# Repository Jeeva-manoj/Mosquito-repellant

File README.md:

# Mosquito-repellant
This EAGLE schematic can be used as a mosquito repellant, using ultrasonic waves

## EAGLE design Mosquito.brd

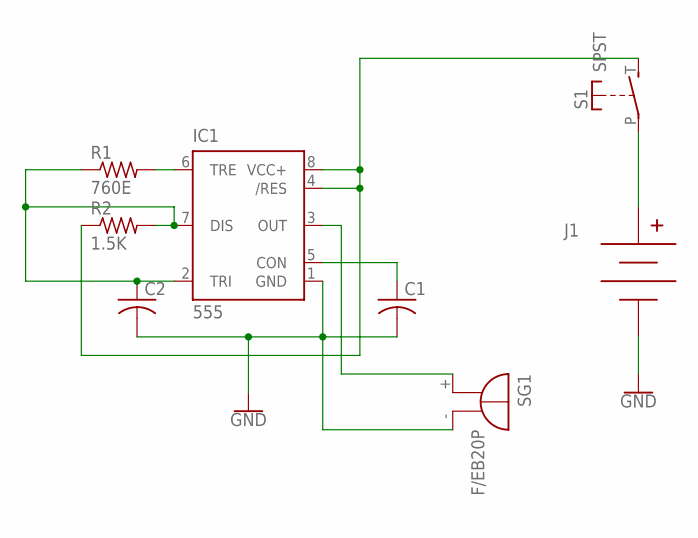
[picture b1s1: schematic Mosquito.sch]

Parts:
C1, C2: C-US025-024X044; C025-024X044
IC1: 555; DIP08
J1: BC9VPC
R1: 760E; 0204V
R2: 1.5K; 0204V
S1: SPST; JUDCOSPST
SG1: F/EB20P

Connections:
GND: C1.2, C2.2, IC1.1 (GND), J1.V-, SG1.-
unnamed: C2.1, IC1.2 (TRI), IC1.7 (DIS), R1.1, R2.2
unnamed: IC1.6 (TRE), R1.2
unnamed: IC1.3 (OUT), SG1.+
unnamed: C1.1, IC1.5 (CON)
unnamed: J1.V+, S1.P
unnamed: IC1.4 (/RES), IC1.8 (VCC+), R2.1, S1.T (S)

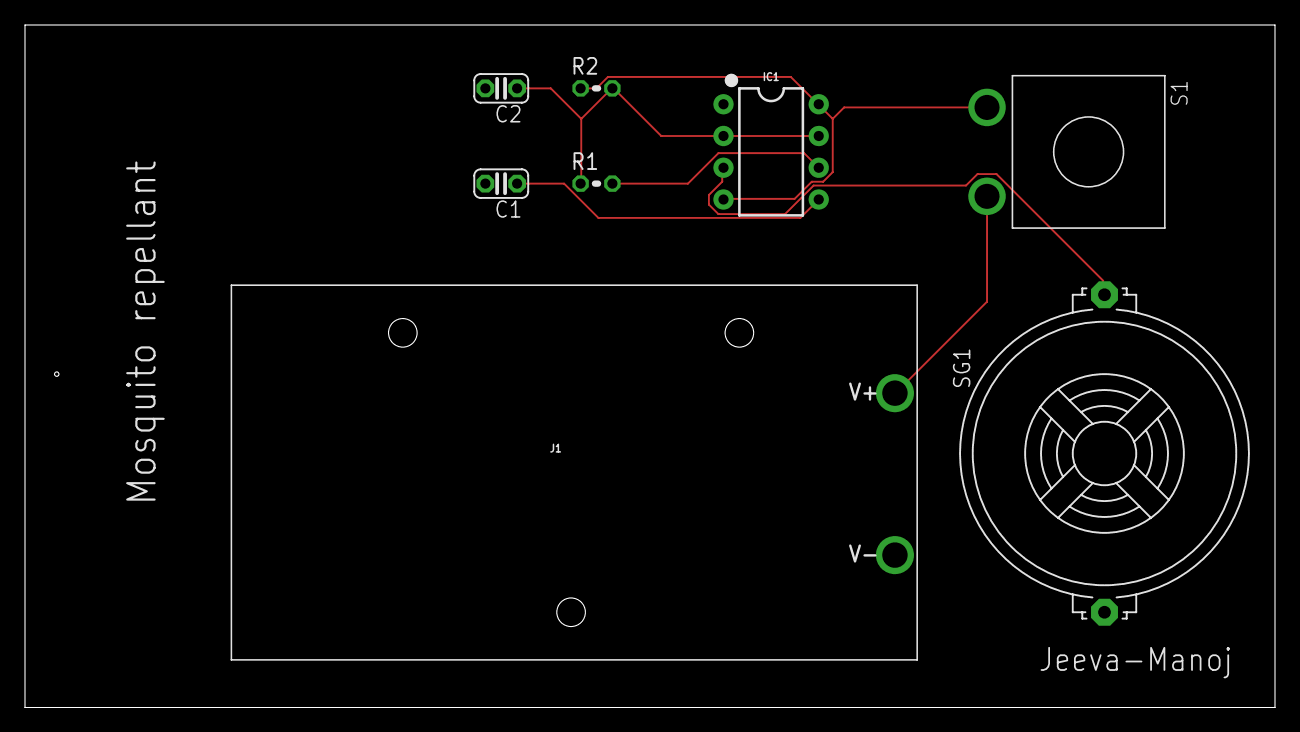
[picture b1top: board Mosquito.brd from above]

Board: 2 copper layers, 100.0 x 54.6 mm, 8 parts (0 on the bottom side), 7 nets.

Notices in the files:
parts and their libraries:
SparkFun-IC-Special-Function: Licensing: Creative Commons ShareAlike 4.0 International - https://creativecommons.org/licenses/by-sa/4.0
